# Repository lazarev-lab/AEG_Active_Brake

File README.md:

# ⚡ AEG Active Brake & Electronic Trigger (MOSFET)

A compact high-performance MOSFET module for Airsoft Electric Guns (AEGs).

The design replaces traditional mechanical trigger contacts with an electronic switching system based on a half-bridge MOSFET driver, improving trigger response, reducing contact wear, and providing active motor braking to minimize overspin.

---

## ✨ Features

### ⚡ Electronic Trigger Switching

Mechanical trigger contacts carry only a low-current control signal while all motor current flows through dedicated power MOSFETs.

**Benefits:**

* Faster trigger response
* No contact arcing
* Increased trigger lifespan
* Lower electrical losses

---

### 🛑 Active Braking

Upon trigger release, the half-bridge actively drives the motor terminals toward the supply rail, rapidly dissipating the motor's rotational energy.

This significantly reduces gearbox overspin and helps prevent unintended double-shots, especially in high-speed builds.

---

### 🔒 Hardware Shoot-Through Protection

The design uses the `LM5106MM` half-bridge gate driver with a fixed **600 ns dead time**.

This hardware-enforced delay guarantees that the high-side and low-side MOSFETs cannot switch simultaneously.

**Benefits:**

* Prevents shoot-through currents
* Protects MOSFETs from failure
* Improves overall reliability

---

### 🛡️ Transient Protection

The circuit includes dedicated protection against voltage spikes generated by the motor.

| Component | Function                                                                         |
| --------- | -------------------------------------------------------------------------------- |
| `SMBJ18A` | Clamps supply voltage transients during switching and braking                    |
| `SS34`    | Provides an additional low-loss current path and suppresses inductive transients |

---

### 📶 Noise-Resistant Trigger Input

The trigger input uses an active-low configuration with a pull-up resistor.

This helps prevent accidental firing caused by:

* Electrostatic discharge (ESD)
* Electromagnetic interference (EMI)
* Floating trigger contacts

---

## ⚙️ Operating Principle

The trigger controls the `HB` input of the `LM5106MM`.

### Trigger Pressed

* `HB = LOW`
* High-side MOSFET OFF
* Low-side MOSFET ON
* Motor energized

### Trigger Released

* `HB = HIGH`
* High-side MOSFET ON
* Low-side MOSFET OFF
* Active braking engaged

The gate driver automatically inserts a fixed 600 ns dead time during every switching transition.

---

## 📊 Technical Specifications

| Parameter         | Value                        |
| ----------------- | ---------------------------- |
| Operating Voltage | 7.4 V – 14.8 V Li-Po (2S–4S) |
| Gate Driver       | `LM5106MM`                   |
| Dead Time         | 600 ns                       |
| Power MOSFETs     | 2 × `GT007N04TL`             |
| TVS Diode         | `SMBJ18A`                    |
| Schottky Diode    | `SS34`                       |
| Trigger Type      | Dry Contact / Microswitch    |
| Active Brake      | Yes                          |

---

## 🔌 Wiring

| Pad         | Connection            |
| ----------- | --------------------- |
| **+Bat**    | Battery Positive (+)  |
| **-Bat**    | Battery Negative (-)  |
| **+Motor**  | Motor Positive (+)    |
| **-Motor**  | Motor Negative (-)    |
| **Buton**   | Trigger Contact       |
| **Buton_2** | Trigger Contact (GND) |

### Trigger Wiring

The trigger simply shorts `Buton` to `Buton_2` when pressed.

---

## ⚠️ Important Notes

### Reverse Polarity

This design does **not** include reverse-polarity protection.

Connecting the battery backwards may permanently damage:

* TVS diode
* Gate driver
* MOSFETs

Always verify wiring before connecting a battery.

### Recommended Batteries

* 2S Li-Po (7.4 V)
* 3S Li-Po (11.1 V)
* 4S Li-Po (14.8 V)

---

## 📂 Repository Structure

```text
.
├── *.kicad_pro     # KiCad project
├── *.kicad_sch     # Schematic
├── *.kicad_pcb     # PCB layout
└── .gitignore      # KiCad-specific ignore rules
```

---

## 🎯 Design Goals

* Fast trigger response
* Reliable active braking
* Compact PCB footprint
* High current capability
* Hardware shoot-through protection
* Low component count
* Easy installation in AEG gearboxes

---

## 📄 License

Released under the **MIT License**.

You are free to use, modify, manufacture, and distribute this design, including commercial use, provided that the original copyright notice and license text are retained.

See the `LICENSE` file for details.

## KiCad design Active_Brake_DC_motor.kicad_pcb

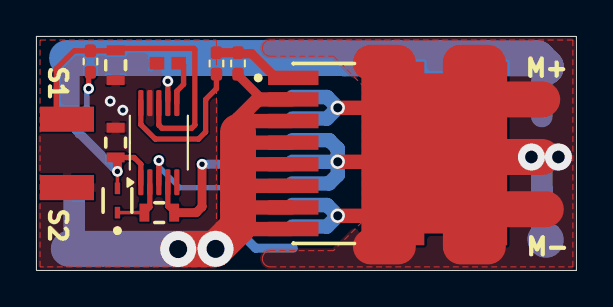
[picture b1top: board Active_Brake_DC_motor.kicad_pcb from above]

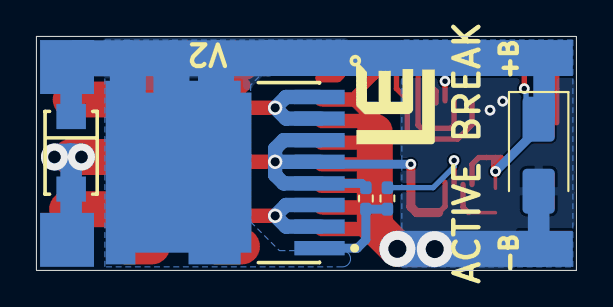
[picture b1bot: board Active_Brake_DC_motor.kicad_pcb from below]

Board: 2 copper layers, 30.0 x 13.0 mm, 21 parts (11 on the bottom side), 10 nets.

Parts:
+B: 3S_PADS_1WAY_1MM; PADS_1WAY_1MM
+M: 3S_PADS_1WAY_1MM; PADS_1WAY_1MM
-B: 3S_PADS_1WAY_1MM; PADS_1WAY_1MM
-M: 3S_PADS_1WAY_1MM; PADS_1WAY_1MM
C1: 1uF; FP-CGA3E-0_3-0_1-IPC_C
C2, C3: 100nF; FP-CGA3E-0_3-0_1-IPC_C
D1: BAT54; FP-SOD-523-MFG
D2: SS34 DO-214AC; FP-SMA-MFG
D3: SMBJ18A; D_SMA
Q1, Q2: GT007N04TL; FP-100CU-MFG
R2, R4: 100K; R_0402_1005Metric_Pad0.72x0.64mm_HandSolder
R3: 100K; 0402_RESC1005N
R5, R6: 10; R_0402_1005Metric_Pad0.72x0.64mm_HandSolder
R7: 2K; R_0402_1005Metric_Pad0.72x0.64mm_HandSolder
S, S1: 3S_PADS_1WAY_1MM; PADS_1WAY_1MM
U1: LM5106MM; VSSOP-10_3x3mm_P0.5mm

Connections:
+Bat: +B.1, +M.1, C1.1, D1.2 (A), D2.1 (K), D3.1 (A1), Q2.9 (D), R7.2, U1.1 (VDD), U1.7 (EN)
-Bat: -B.1, C1.2, C3.2, D3.2 (A2), Q1.2 (S), Q1.3 (S), Q1.4 (S), Q1.5 (S), Q1.6 (S), Q1.7 (S), Q1.8 (S), R3.1, R4.1, S.1, U1.9 (VSS)
-Motor: -M.1, C2.2, D2.2 (A), Q1.9 (D), Q2.2 (S), Q2.3 (S), Q2.4 (S), Q2.5 (S), Q2.6 (S), Q2.7 (S), Q2.8 (S), R2.2, U1.4 (HS)
/Buton: C3.1, R7.1, S1.1, U1.8 (IN)
/HB: C2.1, D1.1 (C), U1.2 (HB)
/HO: R5.2, U1.3 (HO)
/LO: R6.2, U1.10 (LO)
unnamed: Q1.1 (G), R4.2, R6.1
unnamed: Q2.1 (G), R2.1, R5.1
unnamed: R3.2, U1.6 (RDT)

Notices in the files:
README.md:
License: MIT
